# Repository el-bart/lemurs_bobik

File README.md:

# Lemur's Bobik

project of a toy for a 3-5 year child, that is aimed at learning basic programming skills.
robot has 4 buttons for programming directions and one button to start it.

program is generated by a sequence of buttons pressed (eg. forward, forward, left).
after pressing "start" button, robot begins execution of a given sequence.
its programming is thus similar to Logo programming language, but does not require one to be able to read/write, or spending time in front of the screen.

robot's body is designed to mimic a bit autonomous vacuum cleaner robots, that children know and love. :)

## HW parts

* 2x unipolar stepper motors (M42SP-5M - from old desktop printer)
* 12x M3x10 screws
* 12x M3 threaded inserts
* velcro for holding LiPo pack in place (length according to your LiPo size)

## 3D printed parts

`seal` is supposed to be printed in TPU.
after printing, it shall be glued to a `bottom` part with CA glue.
without gluing it will be very hard to put things in place.

all the other elements can be printed in pretty much anything.
my build was just in regular, white PLA.

it's recommend to put some felt under from and rear edges of the bottom part.
it's also worth gluing a thin strip of felt around wheels' external circumference.
this will protect floors from sharp edges and decrease the amount of noise, on flat floors.

while the `seal` is optional, it's highly recommended to silence vibrations.

## electronics

for electronic components checkout BOM, generated by builds, namely:
```
board/hw/control/build/bom.csv
board/hw/buttons/build/bom.csv
```

## known issues

### engines are hard to mount

screws (especially bottom one) are hard to reach.
in a hindsight whole engine-wheel module should have been reworked.
engines could drive wheels directly, and me mounted with threaded inserts.
this would simplify things a lot, and removed noisy gears altogether.

### missing visual feedback

on top panel there should be more LEDs.
these shall indicate:
* button press recorded (possible with dir)
* powered-on state
* low battery state

### batter status

it should be possible to check batter status w/o opening enclosure and disconnecting it.
currently it's very absorbing and inconvenient.

### OTA

programming via AVR's ISP is annoying and requires disassembly.
as of writing these words (HW v2.1) it also requires unplugging main battery (to be fixed in next HW release).
OTA re-flashing would be an improvement.

### debugability

ATtinty2313 in current setting does not have enough pins to provide any feedback (even LED blinking).
more powerful µC should be used instead, that'd allow for serial (or BTLE) port debugging, to monitor state.
on top of that in-system `gdb` would save time for finding stupid mistakes.
this would greatly simplify finding issues and diagnosing inconveniences, that currently require a lot of fuss and re-flashing.

### need better engines

desktop printer engines used require unusual voltage (here: 24V, 0.35A).
they are also quite weak (here: can easily be stopped with 2 fingers).
more powerful NEMA 17 engines would be far superior choice.
using bipolar steppers would also allow to use off the shelve stepper drivers and provide more torque.

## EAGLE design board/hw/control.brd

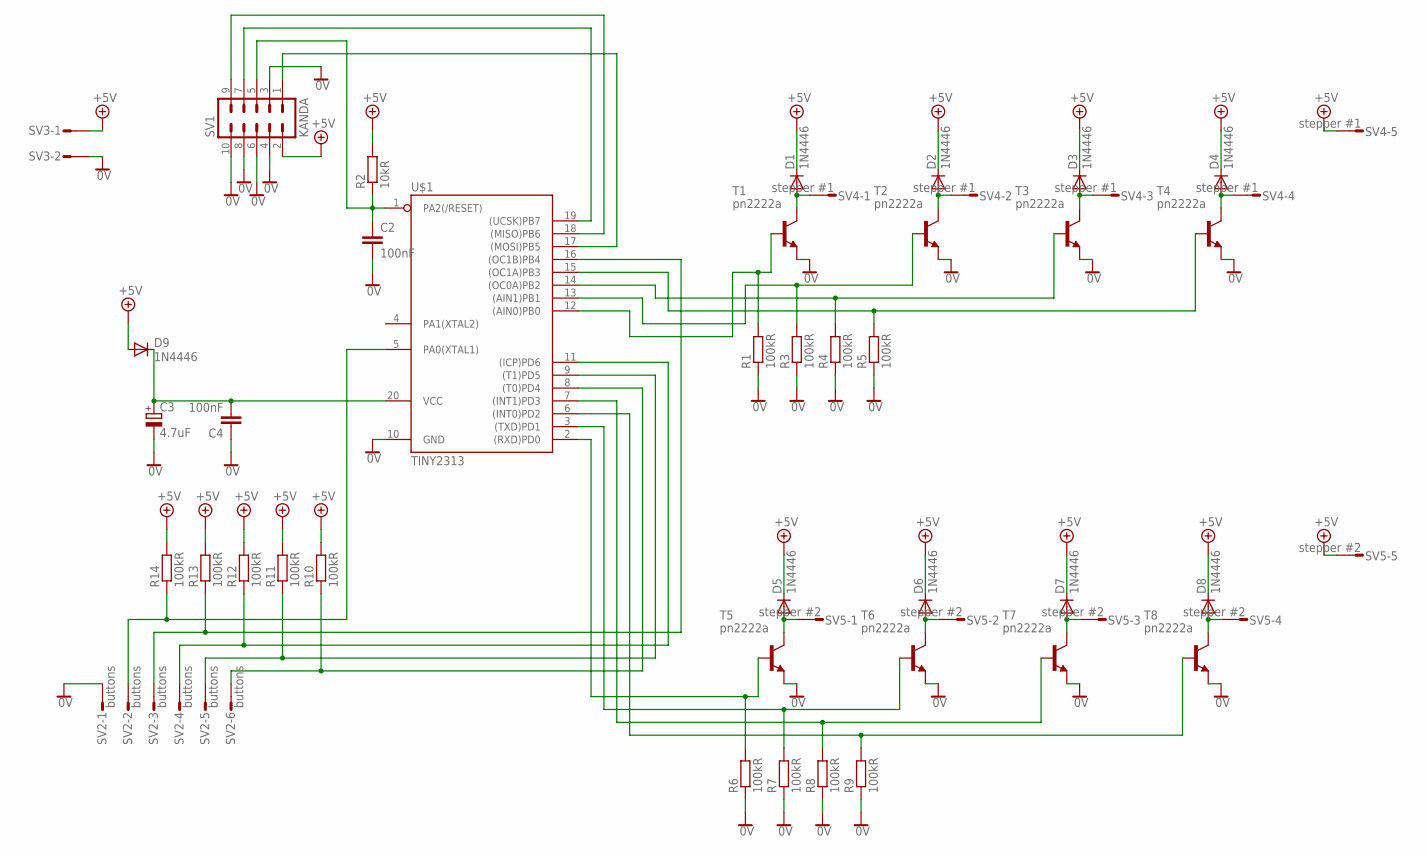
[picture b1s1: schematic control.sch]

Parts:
C2, C4: 100nF; C3216
C3: 4.7uF; 153CLV-0405
D1, D2, D3, D4, D5, D6, D7, D8, D9: 1N4446; DO35-10
R1, R3, R4, R5, R6, R7, R8, R9, R10, R11, R12, R13, R14: 100kR; MINI_MELF-0204W
R2: 10kR; MINI_MELF-0204W
SV1: KANDA; ML10
SV2: buttons; S06P
SV3: S02P
SV4: stepper #1; S05P
SV5: stepper #2; S05P
T1, T2, T3, T4, T5, T6, T7, T8: pn2222a; TO92-CBE
U$1: TINY2313; DIL20

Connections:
0V: C2.2, C3.-, C4.1, R1.1, R3.1, R4.1, R5.1, R6.1, R7.1, R8.1, R9.1, SV1.3, SV1.4, SV1.6, SV1.8, SV1.10, SV2.1, SV3.2, T1.E, T2.E, T3.E, T4.E, T5.E, T6.E, T7.E, T8.E, U$1.10 (GND)
+5V: D1.C, D2.C, D3.C, D4.C, D5.C, D6.C, D7.C, D8.C, D9.A, R2.2, R10.2, R11.2, R12.2, R13.2, R14.2, SV1.2, SV3.1, SV4.5, SV5.5
unnamed: D5.A, SV5.1, T5.C
unnamed: R6.2, T5.B, U$1.2 ((RXD)PD0)
unnamed: R10.1, SV2.6, U$1.8 ((T0)PD4)
unnamed: R7.2, T6.B, U$1.3 ((TXD)PD1)
unnamed: D7.A, SV5.3, T7.C
unnamed: R8.2, T7.B, U$1.7 ((INT1)PD3)
unnamed: D8.A, SV5.4, T8.C
unnamed: D1.A, SV4.1, T1.C
unnamed: R1.2, T1.B, U$1.12 ((AIN0)PB0)
unnamed: D2.A, SV4.2, T2.C
unnamed: R3.2, T2.B, U$1.13 ((AIN1)PB1)
unnamed: D3.A, SV4.3, T3.C
unnamed: R4.2, T3.B, U$1.14 ((OC0A)PB2)
unnamed: D4.A, SV4.4, T4.C
unnamed: R5.2, T4.B, U$1.15 ((OC1A)PB3)
unnamed: C2.1, R2.1, SV1.5, U$1.1 (PA2(/RESET))
unnamed: SV1.1, U$1.17 ((MOSI)PB5)
unnamed: R9.2, T8.B, U$1.6 ((INT0)PD2)
unnamed: SV1.7, U$1.19 ((UCSK)PB7)
unnamed: SV1.9, U$1.18 ((MISO)PB6)
unnamed: D6.A, SV5.2, T6.C
unnamed: R11.1, SV2.5, U$1.9 ((T1)PD5)
unnamed: R12.1, SV2.4, U$1.11 ((ICP)PD6)
unnamed: R13.1, SV2.3, U$1.16 ((OC1B)PB4)
unnamed: R14.1, SV2.2, U$1.5 (PA0(XTAL1))
unnamed: C3.+, C4.2, D9.C, U$1.20 (VCC)

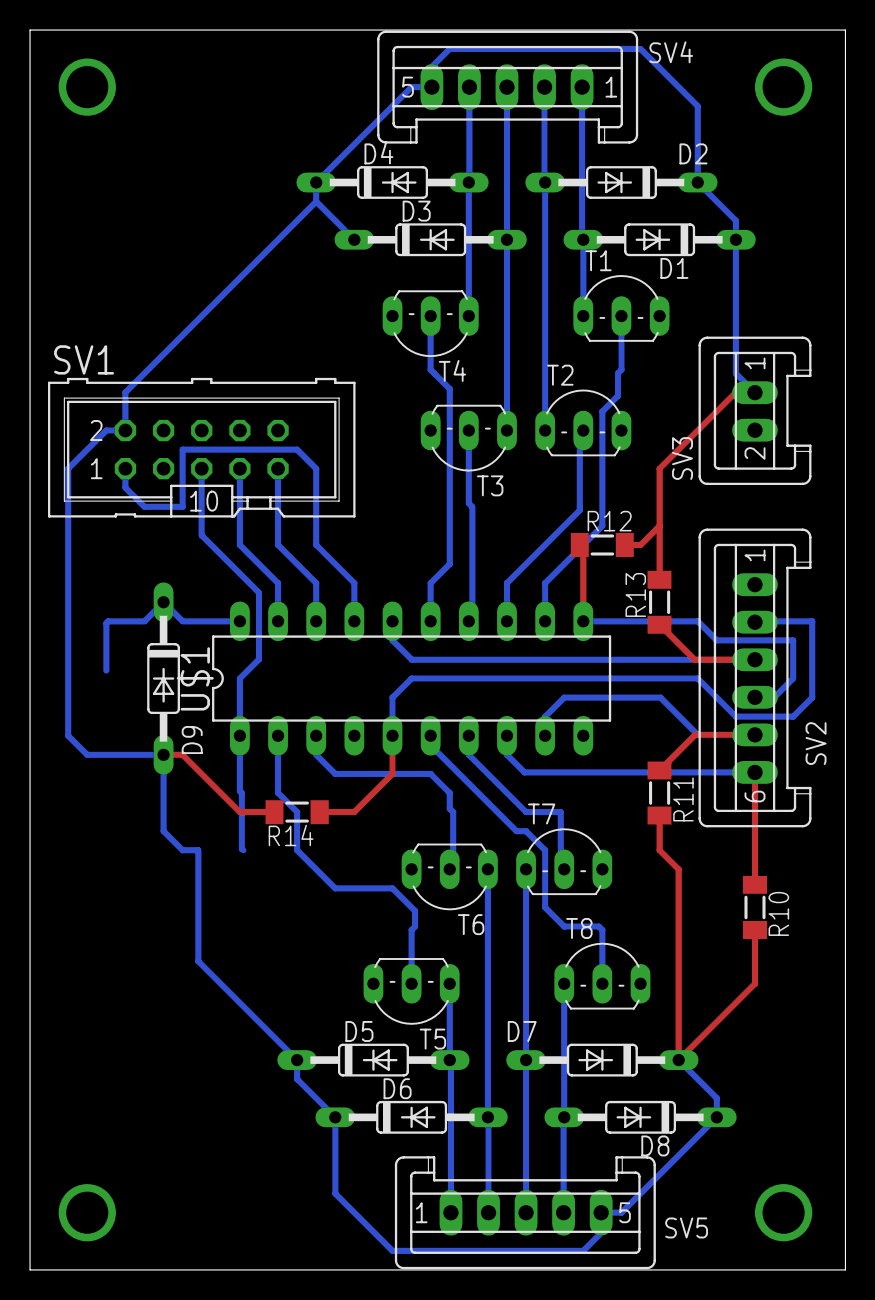
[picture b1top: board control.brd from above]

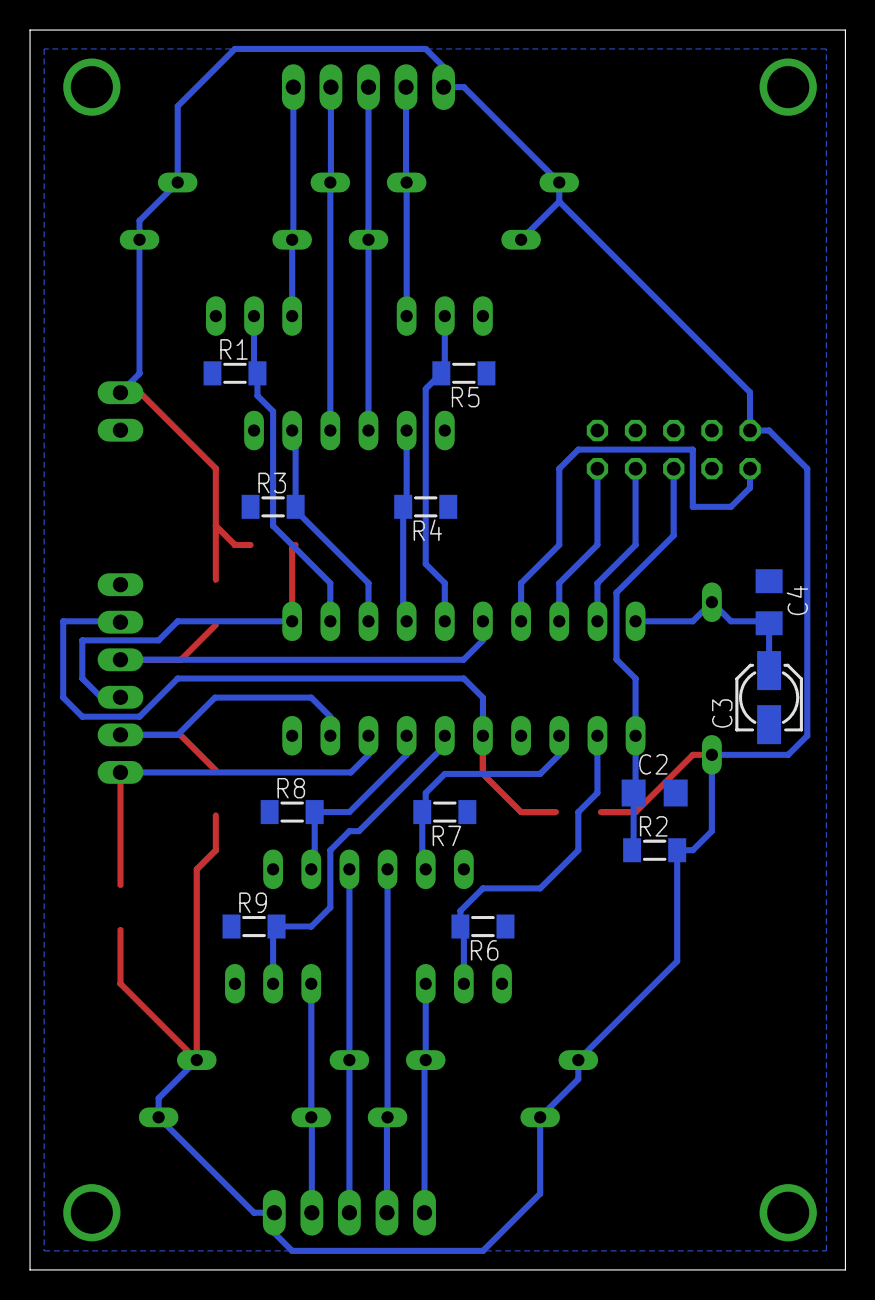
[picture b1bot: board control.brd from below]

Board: 2 copper layers, 54.3 x 82.5 mm, 40 parts (12 on the bottom side), 28 nets.

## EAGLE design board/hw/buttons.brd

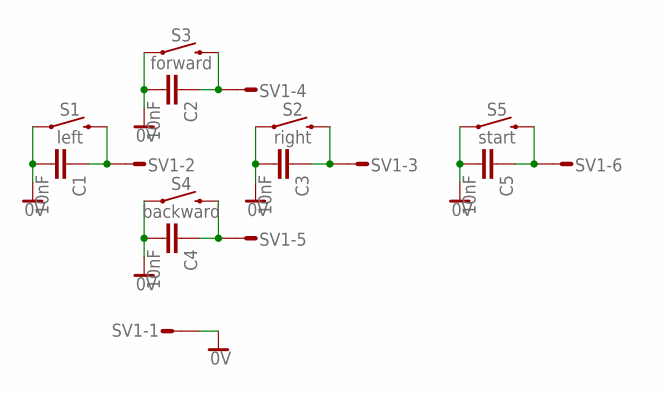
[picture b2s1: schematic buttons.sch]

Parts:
C1, C2, C3, C4, C5: 10nF; C0805K
S1: left; TACTILE_SWITCH_SMD_12MM
S2: right; TACTILE_SWITCH_SMD_12MM
S3: forward; TACTILE_SWITCH_SMD_12MM
S4: backward; TACTILE_SWITCH_SMD_12MM
S5: start; TACTILE_SWITCH_SMD_12MM
SV1: S06P

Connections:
0V: C1.2, C2.2, C3.2, C4.2, C5.2, S1.1, S2.1, S3.1, S4.1, S5.1, SV1.1
unnamed: C1.1, S1.3 (2), SV1.2
unnamed: C3.1, S2.3 (2), SV1.3
unnamed: C2.1, S3.3 (2), SV1.4
unnamed: C4.1, S4.3 (2), SV1.5
unnamed: C5.1, S5.3 (2), SV1.6

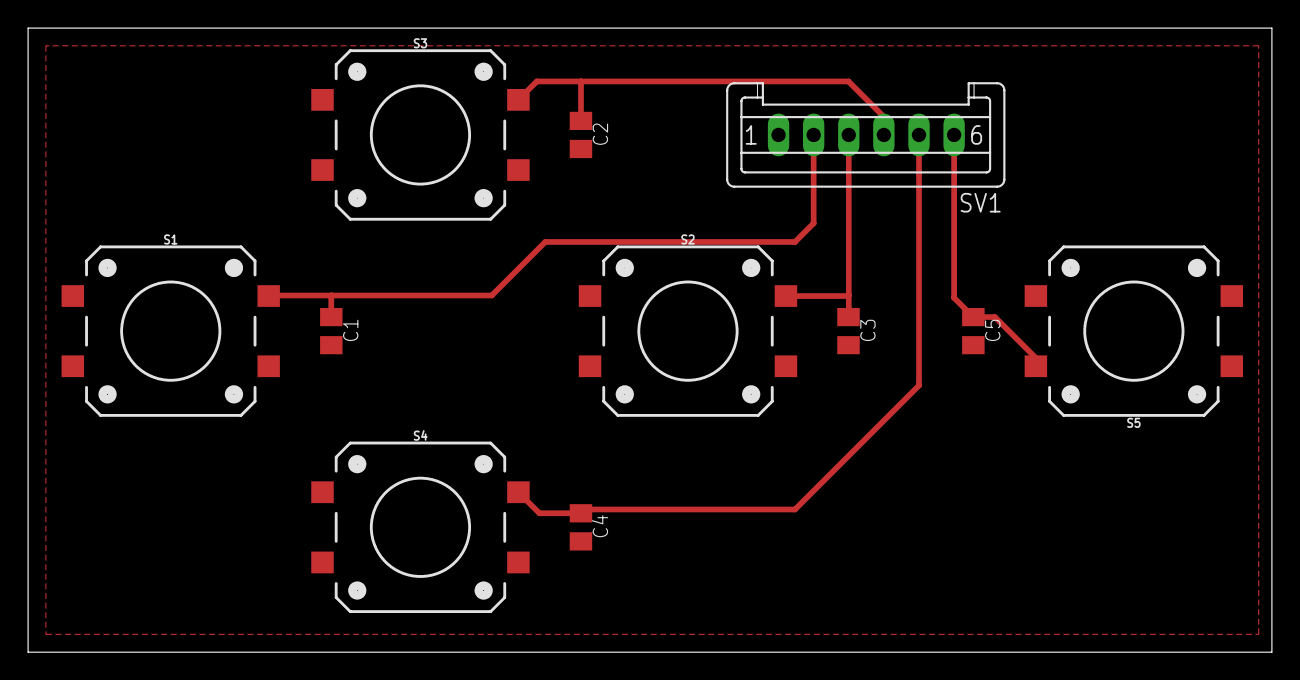
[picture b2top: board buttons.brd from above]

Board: 2 copper layers, 88.6 x 44.4 mm, 11 parts (0 on the bottom side), 6 nets.

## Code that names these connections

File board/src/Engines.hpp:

#pragma once
#include "config.hpp"
#include <util/delay.h>

// LEFT  SEQ: PD0 PD2 PD1 PD3
// RIGHT SEQ: PB0 PB2 PB1 PB3
// min  - 15[ms] per step!
// good - 30[ms] per step!

namespace Engines
{

struct PortB
{
  static void init_bits(uint8_t b)   { DDRB |=  b; }
  static void set_bits(uint8_t b)   { PORTB |=  b; }
  static void clear_bits(uint8_t b) { PORTB &= ~b; }
};


struct PortD
{
  static void init_bits(uint8_t b)   { DDRD |=  b; }
  static void set_bits(uint8_t b)   { PORTD |=  b; }
  static void clear_bits(uint8_t b) { PORTD &= ~b; }
};


template<typename Port, uint8_t B0, uint8_t B1, uint8_t B2, uint8_t B3>
struct Generic
{
  Generic() { Port::init_bits( all_bits() ); }
  void off() { Port::clear_bits( all_bits() ); }
  void step_forward() { go_to_pos( next_pos() ); }
  void step_backward() { go_to_pos( prev_pos() ); }

private:
  static auto all_bits() { return B0 | B1 | B2 | B3; }

  void go_to_pos(uint8_t pos)
  {
    off();
    Port::set_bits( pos2bit(pos) );
    pos_ = pos;
  }

  uint8_t pos2bit(uint8_t pos) const
  {
    switch(pos)
    {
      case 0: return B0;
      case 1: return B1;
      case 2: return B2;
      case 3: return B3;
    }
    return 0xFF;    // should never reach here...
  }

  uint8_t next_pos() const
  {
    if(pos_ < 3)
      return pos_ + 1;
    return 0;
  }

  uint8_t prev_pos() const
  {
    if(0 < pos_)
      return pos_ - 1;
    return 3;
  }

  uint8_t pos_{0};
};


using Left  = Generic<PortD, _BV(3), _BV(1), _BV(2), _BV(0)>;
using Right = Generic<PortB, _BV(3), _BV(1), _BV(2), _BV(0)>;

}

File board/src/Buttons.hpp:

#pragma once
#include "config.hpp"

// BUT_UP:    PD6
// BUT_DOWN:  PB4
// BUT_LEFT:  PD4
// BUT_RIGHT: PD5

// BUT_START: PA0


namespace Buttons
{

inline void init()
{
  DDRA  &= ~_BV(0);
  PORTA |=  _BV(0);

  DDRB  &= ~_BV(4);
  PORTB |=  _BV(4);

  DDRD  &= ~( _BV(4) | _BV(5) | _BV(6) );
  PORTD |=    _BV(4) | _BV(5) | _BV(6);
}


inline bool up_pressed()    { return not (PIND & _BV(6)); }
inline bool down_pressed()  { return not (PINB & _BV(4)); }
inline bool left_pressed()  { return not (PIND & _BV(4)); }
inline bool right_pressed() { return not (PIND & _BV(5)); }
inline bool start_pressed() { return not (PINA & _BV(0)); }

inline bool any_pressed()
{
  return up_pressed()    ||
         down_pressed()  ||
         left_pressed()  ||
         right_pressed() ||
         start_pressed();
}

}

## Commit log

2020-04-20 list of ignored elements - basic stuff
2020-04-20 project description
2020-04-20 build for OpenSCAD models
2020-04-20 gear part
2020-04-20 added some basic prints for elements
2020-04-20 ignoring build itme report files
2020-04-20 gear part is a bit more precise with longer teeth + added rod wole in the center
2020-04-20 decreased drive rod hole + added 2 elements on 1 print
2020-04-21 renamed body to enclosure (more accurate)
2020-04-21 build for sw
2020-04-21 simple watchdog wrapper
2020-04-21 application draft
2020-04-21 updated fuse bits to actual project settings
2020-04-21 moved sources next to hardware schematics + added draft of a control board (schematics for now)
2020-04-21 buttons board is ready
2020-04-21 removed capacitors for buttons - these are already covered by the external board
2020-04-21 single-layer routing completed (yay)
2020-04-21 moved KANDA connector in order to simplifiy and reduce board a bit
2020-04-22 decreased board size to cover only copper part
2020-04-23 added 10nF to button boards capacitors
2020-04-23 reorganized labels, so that these fit on the board
2020-04-23 more labels moved not to collide
2020-04-23 moved everything to a bottom layer
2020-04-23 added note on the board, with version
2020-04-23 added board name to a caption
2020-04-24 placeholders for next elements
2020-04-24 main hull + wheel axis mounts
2020-04-24 wheels hole is now bigger and wider
2020-04-24 added engine mounts
2020-04-25 added missing power supply connector
2020-04-28 ignording *.tmp files
2020-04-28 element that can regulat engine mount
2020-04-28 2x engine mount printed at once
2020-04-29 fixed axis diameters/radiuses
2020-04-29 added battery pack mount
2020-04-29 increased height of bobik, so that wheels squeeze in
2020-04-29 added buttons and control board + moved battery pack closer to the center
2020-04-29 electronic mocks added to VCS
2020-04-29 electronics mocks are now printable
2020-04-29 added screw holders for top part + bottom balancing elements
2020-04-29 added reinforcements on the bottom, for better structural rigidity
2020-04-30 bed temperature 60*C -> 50*C as it works far better on large-scale prints
2020-04-30 extrusion width back to 100% decreased 'unstucking' of the PLA on 1st layer
2020-04-30 back to 102% extrusion - it is ok. the unstucking problem was solved with dimafix
2020-05-09 bed tempaerture @ 55*C
2020-07-09 changed ISP programmer type
2020-07-09 moved to internal 128kHz RC oscilator - should be enough i guess
2020-07-09 led blinking equivalnet for start
2020-07-09 Revert "moved to internal 128kHz RC oscilator - should be enough i guess" turned out that 128kHz is TOO SLOW for my progreammer; 1MHz is a must...
    This reverts commit 048d5ced6bc6437dfce4def79e8d7f2b64772a78.
2020-07-09 split target for flashing fuse bits from flashing firmware
2020-07-09 engine spinning test added
2020-07-09 added some test code for buttons - these will need a bit more extra work in HW (pull-ups missing)
2020-07-10 added all the buttons for testing
2020-07-10 added auto-disable all the engines, once the button look is done
2020-07-10 added missing pull-up 100k Rs for all buttons
2020-07-14 added example code that uses all the buttons
2020-07-14 added helper function that tells if any button was pressed
2020-07-14 removed unused header
2020-07-14 engines are now a separate entity
2020-07-14 enabled watchdog
2020-07-14 helper enum with all the directions
2020-07-14 up/down -> fwd/rev
2020-07-14 added algo for reading program from button presses
2020-07-14 main loop consists of simple function calls only, now
2020-07-14 main program execution loop
2020-07-14 removed dead code from main.cpp
2020-07-14 added possiblity to abort program with any button pressed
2020-07-14 watchdog is now namespace not a class + created EnginesControl helper class
2020-07-14 added automatic turning off of all engines when algorithm is stopped (ended or interrupted)
2020-07-14 added a separate function for turning off() engines, as it is used in two places
2020-07-14 extracted steps counts into config.hpp
2020-07-15 correct values for steps per forward/backward and left/right turn
2020-07-15 fixed forward/backward sequences mix
2020-07-16 external gears generation module
2020-07-16 moved to gear ratio 15:20 (i.e. 0.75), for improved speed
2020-07-16 gears.scad is a dependency thus no model is generated for it
2020-07-16 commented out test gear
2020-07-17 build update for OpenSCAD
2020-07-17 removed unused placeholder file
2020-07-17 list of TODOs
2020-07-17 restored original test example parameters
2020-07-17 decreased number of teeth in gears, so that they are smaller and can fit into an existing frame
2020-07-17 scaled the hole so that it fits the actual wheel
2020-07-18 breaking program is now more responsive (1ms instead of 30ms check)
2020-07-18 added wait for all buttons realeased before starting programming + shorter wait for any pressed state
2020-07-18 added extra functionality for waiting for a button press to become a stable one, before declaring it pressed
2020-07-18 decreased ratio to 20:9 (~2.2)
2020-07-18 moving back to original wheel design, just with a ratio around 2.7 instead of 5.4
2020-07-19 moved hole a bit to front, so that smaller gear on the wheel can be compenstated
2020-07-19 new ratio == less steps needed per op
2020-07-20 restored back wheels from before making gear-ratio changes. steppers used are too weak to handle smaller ratios, aspecially on a non-flat surfaces
2020-07-20 removed TODO for decreased gear ratio - did not work out
2020-07-20 Revert "new ratio == less steps needed per op"
    This reverts commit 329b52fe011198930ef57d2dc42e6798ceef3834.
2020-07-26 increased resolution on certain round elements
2020-07-26 TODO for reset button and change of stepper motors
2020-07-26 typos fixes + covid-19 note for parts selsection
2020-07-26 added map cap block, with rounded edges
2020-07-26 added placeholder for cap holes
2020-08-02 top cap model
2020-08-02 MD5 computing support
2020-08-02 ignoring MD5 generated files
2020-08-03 added arrows and start/stop button
2020-08-03 moved capacitor hole closed to the button (where it should be) + fixed main part's resolution
2020-08-03 replaced hardcoded value with a math to get it, so that it is more visible where it comes from
2020-08-03 buttons are now standing out, not being cut-in
2020-08-03 added laser range-finder mock
2022-07-10 fixed typo in TODO.md
2022-07-10 TODO to add some LEDs
2022-07-10 added some photos of the assemly and a final robot, compared to original cleaning robot
2022-07-10 added images to README.md
2023-11-25 updated SDK an set to build in PLA/precise
2023-11-25 moved mocks to detail/
2023-11-25 increased top screw hole diameter, to make a loose fit for M3 bolt
2023-11-25 mock of the stepper motor
2023-11-25 parts list updated (+TODO)
2023-11-25 buttons baord imported into KiCad
2023-11-25 KiCad SDK for buttons
2023-11-25 removed old KiCad project
2023-11-25 control board has been ported to KiCad
2023-11-25 KiCad SDK
2023-11-25 removing old Eagle CAD project of the ctrl board
2023-11-25 holes are no longer highlighted
2023-11-25 moved old stepper motor mock in place of NEMA 17
2023-11-25 removed SDK - it only works for older KiCad
2023-11-25 ground plane is now populated
2023-11-25 added threaded inserts slots for all screws
2023-11-25 TODO: LiPo pack holder
2023-11-25 removed holes for balancing elements - sticking in felt works well enough
2023-11-25 TODO done: threaded inserts are now avaialble
2023-12-02 KiCad automation SDK for both boards
2023-12-02 buttons board converted to newr KiCad
2023-12-02 ctrl board coverted to newer KiCad
2023-12-02 yet one more backup file type...
2023-12-02 moved most elements from Eagle to KiCad libraries
2023-12-02 removed unused elements and added proper AVR-ISP-10 conector
2023-12-02 assigned correct sizes of elements + some draft positioning; still need to add power management cirtcuitry
2023-12-26 added p-mosfet and zerenrs for power ctrl via buttons, too
2023-12-26 PCB routing mostly done - DRC is WIP
2023-12-26 fixed all DRC errors and most warnings
2023-12-26 no more warnings + realigned some silkscreens
2023-12-26 re-enabled all warnings and fixed siklscreen overlapping items
2023-12-26 'stepper #1' silk rotated correctly
2023-12-26 vias for screws moved to MountingHole, so that it's clearly visible in 3D preview
2023-12-26 added control PCB model generated from KiCad
2023-12-26 added mount holes instead of vias + associated mess
2023-12-26 mountholes adjusted to better match existing 3D mount points on the model
2023-12-26 fixed track widths for power lines to steppers
2023-12-26 marked solved TODOs
2023-12-26 added power-on LED to +5V line
2023-12-26 replaced P-MOSFET with N-MOSFET to maintain power-on state
2023-12-26 added PowerCtrl - for now always-on
2023-12-26 implemented auto-power-off when no program is entered withing 2[min]
2023-12-26 no-timeout condition is now a bit more explicit
2023-12-26 update bipolar engine name
2023-12-26 added some more exclusions
2023-12-26 removed TODO, as all's done + updated description to reflect new PCB design
2023-12-26 KiCad SDK updated to latest
2023-12-27 updated KiCad SDK to version exporting drills with gerber, too
2024-01-12 page size adjusted to schematics requirements
2024-01-12 sorking BOM instances
2024-01-13 adjusted programming speed to match µC
2024-01-13 flasing at 1/4 µC's speed, as suggested by datasheet
2024-01-13 fixed bug with not counting timeout properly
2024-01-13 removed dead code
2024-01-13 decreased stepper motors' step delay - with proper power supply we can go much faster
2024-01-14 engines directions are swaped
2024-01-14 increased buttons sensitivity
2024-01-14 fine-tuned moving speed
2024-01-14 TODO to optimize keyboard usage
2024-01-14 C2 and C4 are not 1206 as they should
2024-01-14 re-filled zones
2024-01-14 project updated
2024-01-14 removed old battery pack holder
2024-01-14 batter slot is now for velcro + LiPo pack
2024-01-14 added note on velcro for holding LiPo
2024-01-14 added FAQ section
2024-01-14 updated list of screws and nuts + BOM for electronic components
2024-01-14 updated pictured and removed (now outdated) FAQ
2024-01-14 removed FAQ (this time for real)
2024-01-14 electornics moved to a separate section
2024-01-14 updated PCB version
2024-01-14 improved input buttons filtering, to ensure more responsive (and reliable) input
2024-01-14 fixed the issue where wake-up button press was not added to program sequence
2024-01-14 decreased speed of steppers a bit
2024-01-14 added exact type of steppers
2024-01-14 adjusted travelved dsistance params
2024-01-14 decreased number of directions to 30 (RAM)
2024-01-14 more draconian accurate algo of reading key presses
2024-01-14 lsessions learned / known issues
2024-01-14 adjusted for forward-steps
2024-01-14 yet another buttons tunning
2024-01-14 added diade so that AVR's ISP can optionaly power the board, but board power will not damage the programmer
2024-01-16 perfect 360*deg turn :)
2024-01-23 KiCad SDK v2.2
2024-01-24 moved common numbers into shared code part
2024-01-24 added seal model
2024-01-24 aggresive usage of m3d's fn() for faster previews
2024-01-24 added cylinder_h as a common param, too
2024-01-24 renamed main module to align with file name + removed bottom visuzalitaion
2024-01-24 added visualizatrion of both top() and seal() in preview
2024-01-24 added preview of top and seal by default
2024-01-24 3D SDK upgrade
2024-01-24 pcb_control.stl is now to be copied from the control board's build
2024-01-24 printing seal in TPU, solid but w/o ironing, as it does not need to be waterproof - it's just about shock absorbtion
2024-01-25 some hints on 3D printed elements and felt placement
2024-09-20 fixed a couple typos
2024-09-20 KiCad SDK update for buttons board
2024-09-20 KiCad SDK update for control board

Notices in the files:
parts and their libraries:
SparkFun-Switches: Licensing: Creative Commons ShareAlike 4.0 International - https://creativecommons.org/licenses/by-sa/4.0
